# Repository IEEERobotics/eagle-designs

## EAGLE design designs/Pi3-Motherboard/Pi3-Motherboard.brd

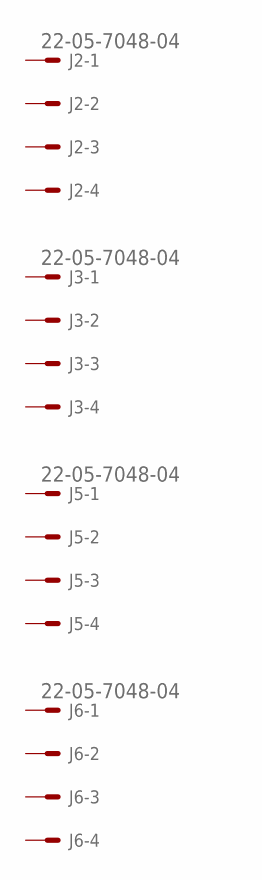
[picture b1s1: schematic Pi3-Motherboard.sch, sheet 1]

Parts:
J2, J3, J5, J6: 22-05-7048-04; 7395-04

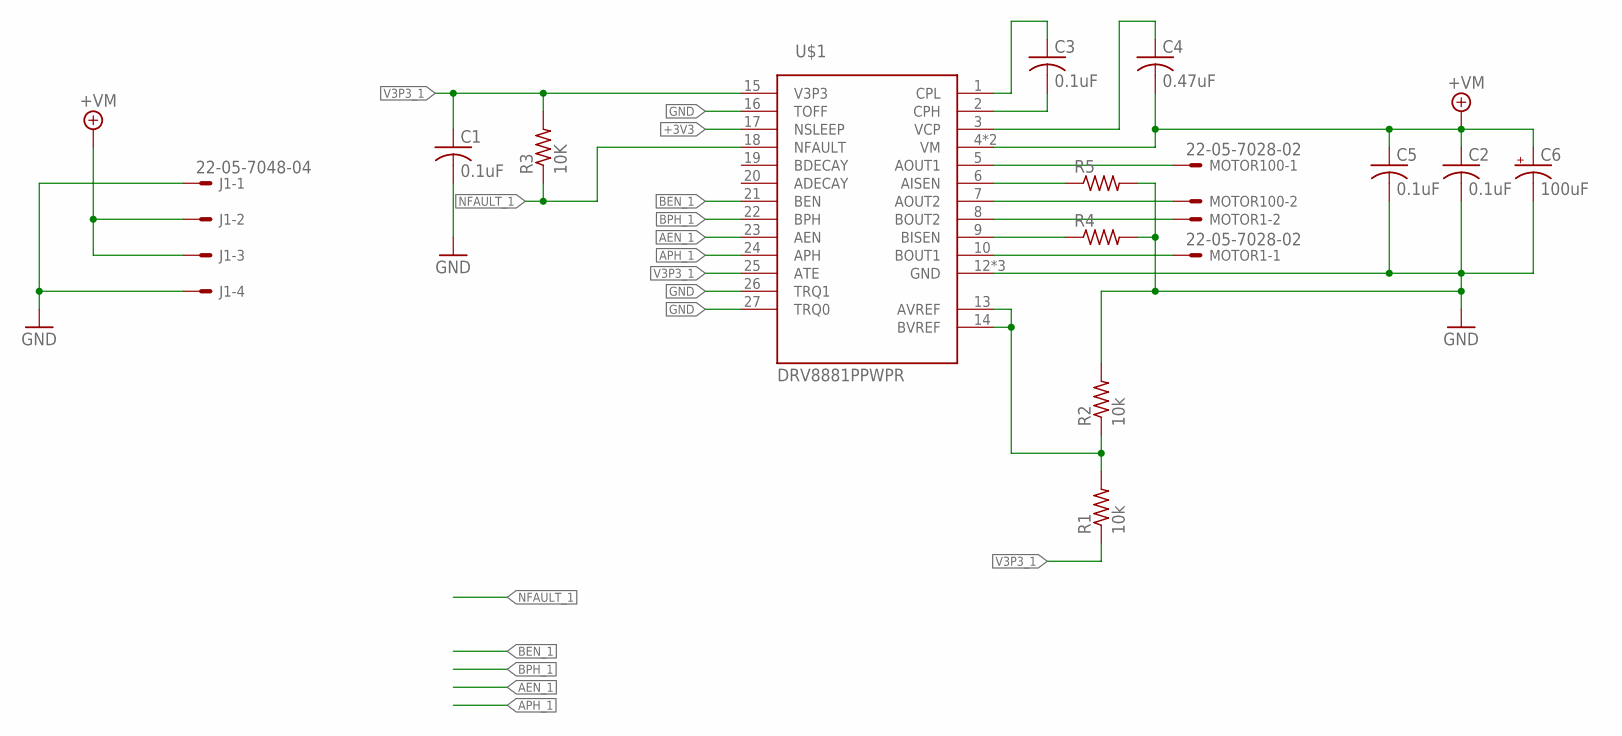
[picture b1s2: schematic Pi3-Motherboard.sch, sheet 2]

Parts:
C1, C2, C3, C5: 0.1uF; C0402
C4: 0.47uF; C0402
C6: 100uF; EIA7343
J1: 22-05-7048-04; 7395-04
MOTOR1, MOTOR100: 22-05-7028-02; 7395-02
R1, R2: 10k; R0402
R3: 10K; R1206
R4, R5: R-US_R1206; R1206
U$1: DRV8881PPWPR; TSSOP-28

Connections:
+3V3: U$1.17 (NSLEEP); also elsewhere on the board
+7V: C2.1, C4.2, C5.1, C6.A (+), J1.2, J1.3, U$1.4 (VM), U$1.11 (VM); also elsewhere on the board
AEN_1: U$1.23 (AEN)
APH_1: U$1.24 (APH)
BEN_1: U$1.21 (BEN)
BPH_1: U$1.22 (BPH)
GND: C1.2, C2.2, C5.2, C6.C (-), J1.1, J1.4, R2.2, R4.2, R5.2, U$1.12 (GND), U$1.16 (TOFF), U$1.26 (TRQ1), U$1.27 (TRQ0), U$1.28 (GND), U$1.EXP (GND); also elsewhere on the board
unnamed: R4.1, U$1.9 (BISEN)
unnamed 32: R5.1, U$1.6 (AISEN); also elsewhere on the board
unnamed: MOTOR100.1, U$1.5 (AOUT1)
unnamed: MOTOR100.2, U$1.7 (AOUT2)
unnamed: MOTOR1.2, U$1.8 (BOUT2)
unnamed: MOTOR1.1, U$1.10 (BOUT1)
unnamed: C3.2, U$1.2 (CPH)
unnamed: C3.1, U$1.1 (CPL)
unnamed: C4.1, U$1.3 (VCP)
unnamed: R1.2, R2.1, U$1.13 (AVREF), U$1.14 (BVREF)
NFAULT_1: R3.1, U$1.18 (NFAULT)
V3P3_1: C1.1, R1.1, R3.2, U$1.15 (V3P3), U$1.25 (ATE)

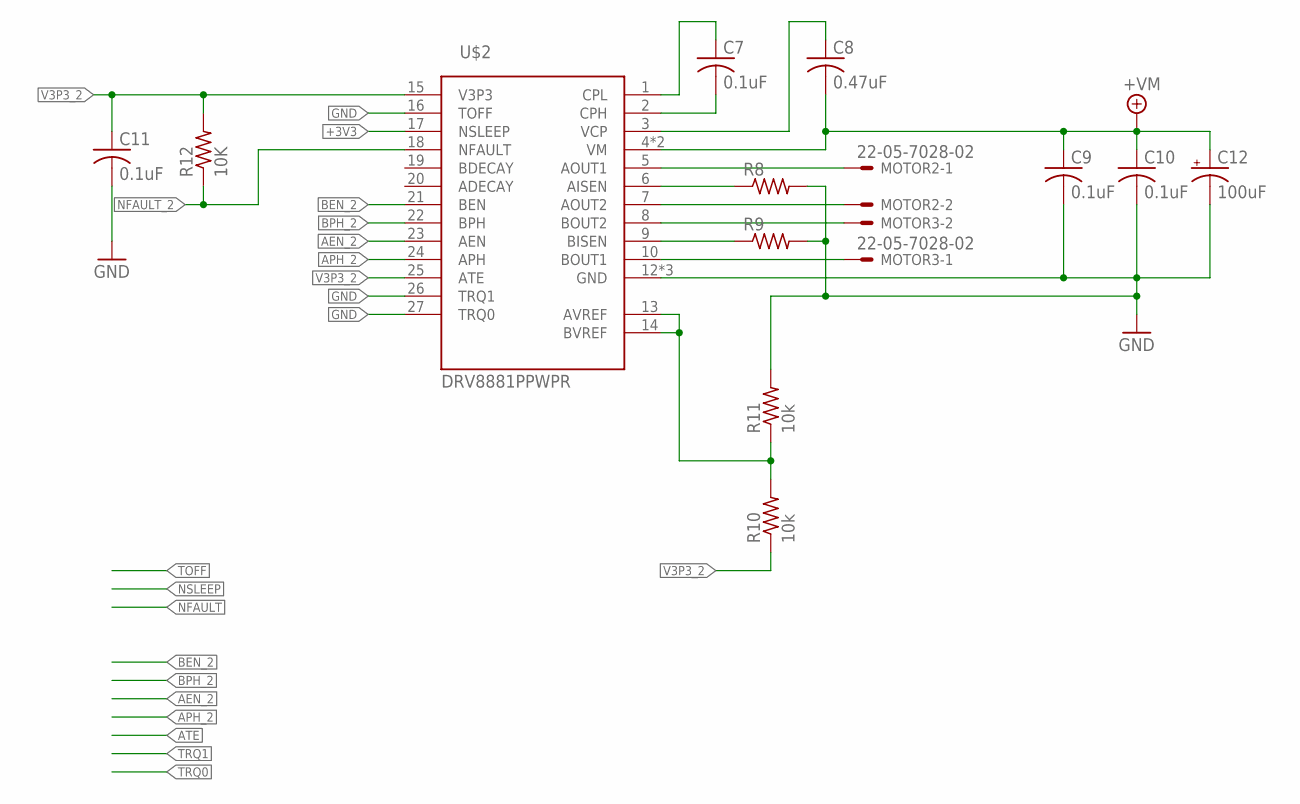
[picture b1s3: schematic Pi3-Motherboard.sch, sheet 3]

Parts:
C7, C9, C10, C11: 0.1uF; C0402
C8: 0.47uF; C0402
C12: 100uF; EIA7343
MOTOR2, MOTOR3: 22-05-7028-02; 7395-02
R8, R9: R-US_R1206; R1206
R10, R11: 10k; R0402
R12: 10K; R1206
U$2: DRV8881PPWPR; TSSOP-28

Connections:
+3V3: U$2.17 (NSLEEP); also elsewhere on the board
+7V: C8.2, C9.1, C10.1, C12.A (+), U$2.4 (VM), U$2.11 (VM); also elsewhere on the board
AEN_2: U$2.23 (AEN)
APH_2: U$2.24 (APH)
BEN_2: U$2.21 (BEN)
BPH_2: U$2.22 (BPH)
GND: C9.2, C10.2, C11.2, C12.C (-), R8.2, R9.2, R11.2, U$2.12 (GND), U$2.16 (TOFF), U$2.26 (TRQ1), U$2.27 (TRQ0), U$2.28 (GND), U$2.EXP (GND); also elsewhere on the board
unnamed: R9.1, U$2.9 (BISEN)
unnamed: R8.1, U$2.6 (AISEN)
unnamed: MOTOR2.1, U$2.5 (AOUT1)
unnamed: MOTOR2.2, U$2.7 (AOUT2)
unnamed: MOTOR3.2, U$2.8 (BOUT2)
unnamed: MOTOR3.1, U$2.10 (BOUT1)
unnamed: C7.2, U$2.2 (CPH)
unnamed: C7.1, U$2.1 (CPL)
unnamed: C8.1, U$2.3 (VCP)
unnamed: R10.2, R11.1, U$2.13 (AVREF), U$2.14 (BVREF)
NFAULT_2: R12.1, U$2.18 (NFAULT)
V3P3_2: C11.1, R10.1, R12.2, U$2.15 (V3P3), U$2.25 (ATE)

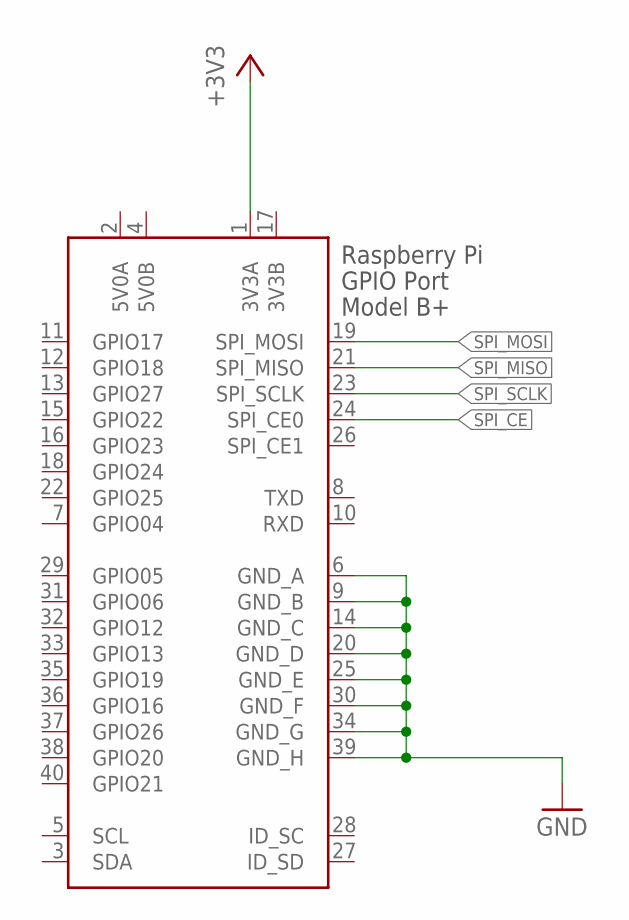
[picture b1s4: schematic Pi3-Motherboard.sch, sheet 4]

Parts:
X1: RASPI_BOARD_B+#_HD; RASPI_BOARD_B+HAT_DF

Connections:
3V3B: X1.17 (3V3B)
5V0A: X1.2 (5V0A)
5V0B: X1.4 (5V0B)
+3V3: X1.1 (3V3A); also elsewhere on the board
GND: X1.6 (GND_A), X1.9 (GND_B), X1.14 (GND_C), X1.20 (GND_D), X1.25 (GND_E), X1.30 (GND_F), X1.34 (GND_G), X1.39 (GND_H); also elsewhere on the board
SPI_CE: X1.24 (SPI_CE0)
SPI_MISO: X1.21 (SPI_MISO)
SPI_MOSI: X1.19 (SPI_MOSI)
SPI_SCLK: X1.23 (SPI_SCLK)

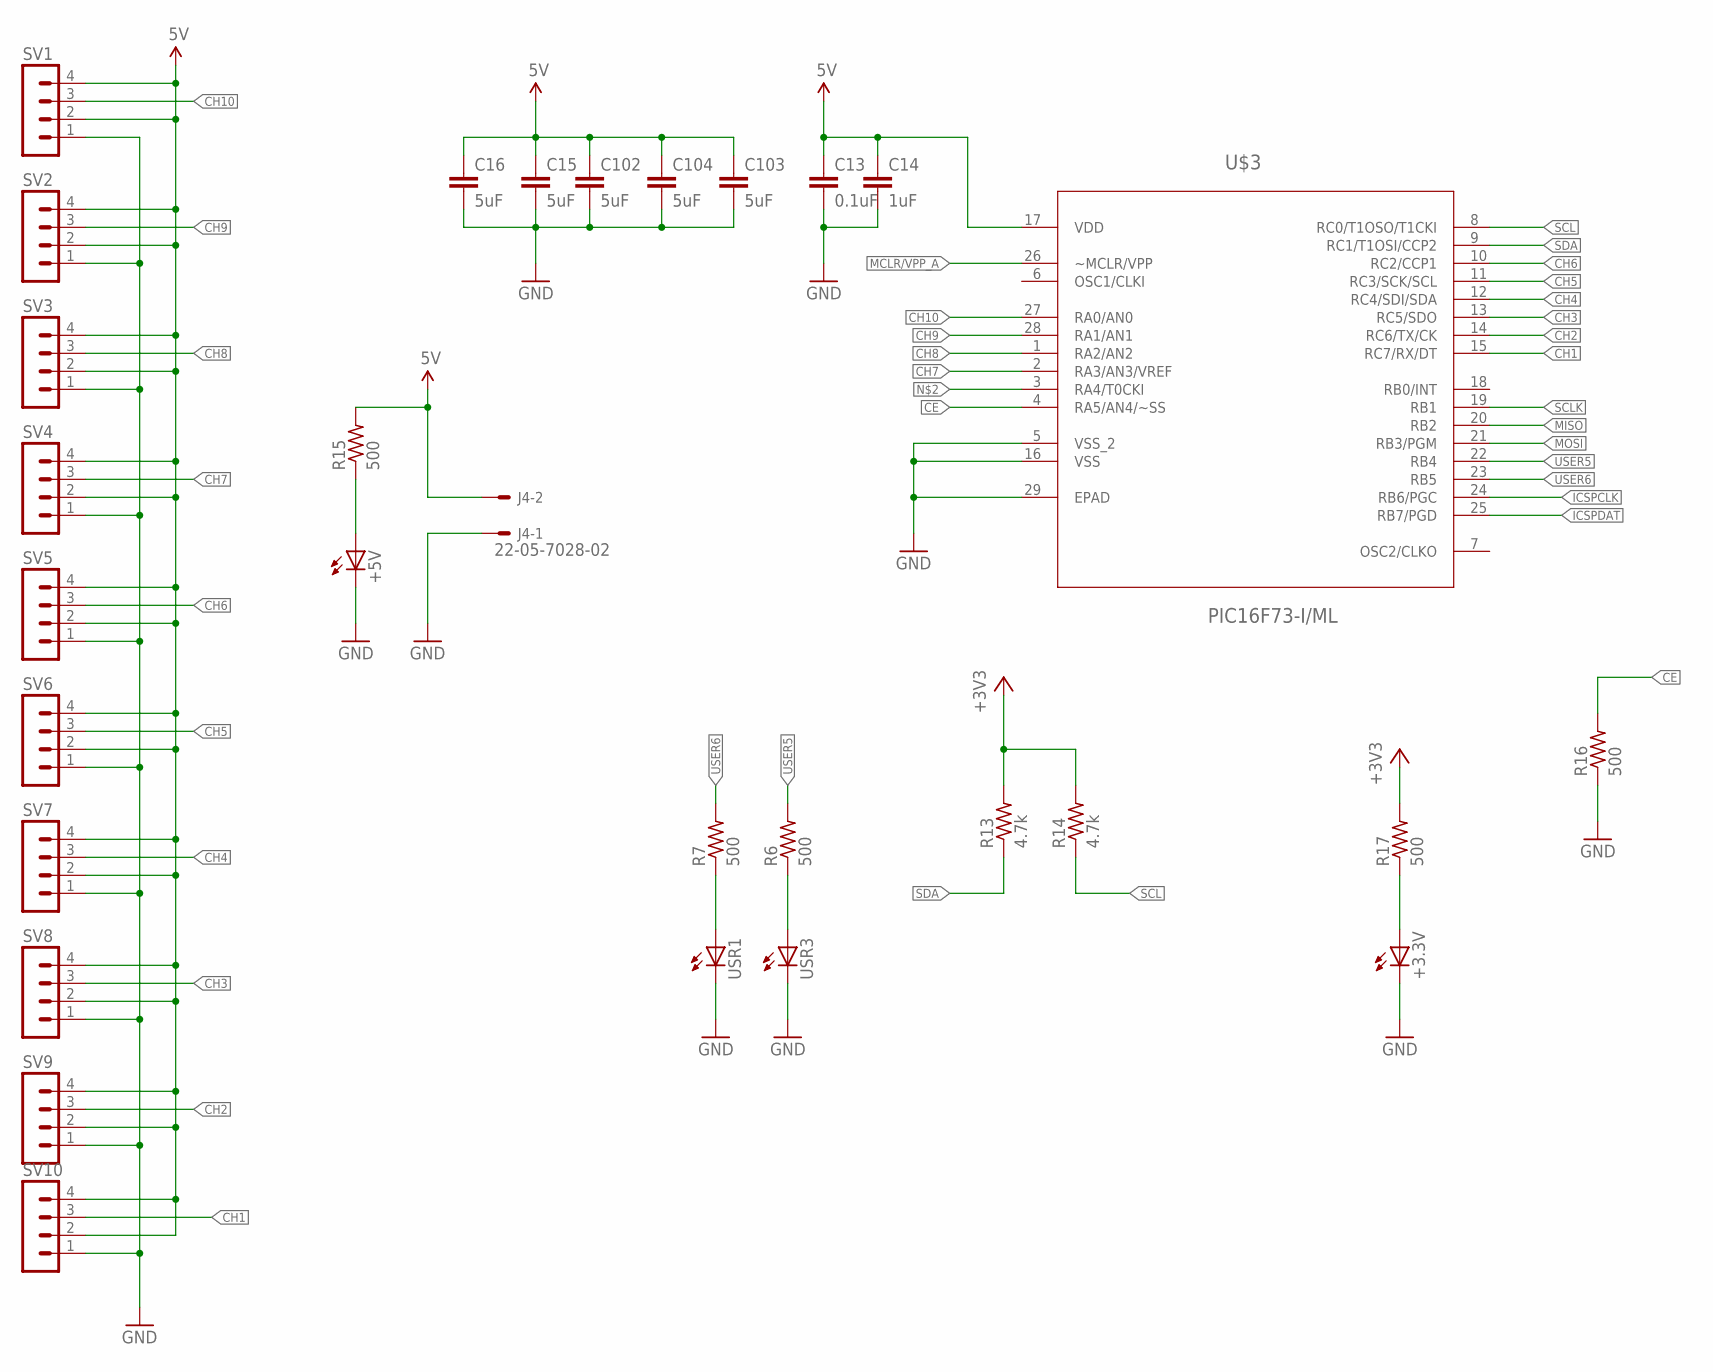
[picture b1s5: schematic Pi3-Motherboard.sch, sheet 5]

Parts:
+3.3V, +5V: LEDCHIP-LED0603; CHIP-LED0603
C13: 0.1uF; C0402
C14: 1uF; C0402
C15, C16, C102, C103, C104: 5uF; C0402
J4: 22-05-7028-02; 7395-02
R6, R7, R15, R16, R17: 500; R0402
R13, R14: 4.7k; R0402
SV1, SV2, SV3, SV4, SV5, SV6, SV7, SV8, SV9, SV10: MA04-1
U$3: PIC16F73-I/ML; QFN65P600X600X100-28N
USR1, USR3: LEDCHIP-LED0603; CHIP-LED0603

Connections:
5V: C13.1, C14.1, C15.1, C16.1, C102.1, C103.1, C104.1, J4.2, R15.2, SV1.2, SV1.4, SV2.2, SV2.4, SV3.2, SV3.4, SV4.2, SV4.4, SV5.2, SV5.4, SV6.2, SV6.4, SV7.2, SV7.4, SV8.2, SV8.4, SV9.2, SV9.4, SV10.2, SV10.4, U$3.17 (VDD)
+3V3: R13.2, R14.2, R17.2; also elsewhere on the board
CE: R16.2, U$3.4 (RA5/AN4/~SS)
CH1: SV10.3, U$3.15 (RC7/RX/DT)
CH2: SV9.3, U$3.14 (RC6/TX/CK)
CH3: SV8.3, U$3.13 (RC5/SDO)
CH4: SV7.3, U$3.12 (RC4/SDI/SDA)
CH5: SV6.3, U$3.11 (RC3/SCK/SCL)
CH6: SV5.3, U$3.10 (RC2/CCP1)
CH7: SV4.3, U$3.2 (RA3/AN3/VREF)
CH8: SV3.3, U$3.1 (RA2/AN2)
CH9: SV2.3, U$3.28 (RA1/AN1)
CH10: SV1.3, U$3.27 (RA0/AN0)
GND: +3.3V.C, +5V.C, C13.2, C14.2, C15.2, C16.2, C102.2, C103.2, C104.2, J4.1, R16.1, SV1.1, SV2.1, SV3.1, SV4.1, SV5.1, SV6.1, SV7.1, SV8.1, SV9.1, SV10.1, U$3.5 (VSS_2), U$3.16 (VSS), U$3.29 (EPAD), USR1.C, USR3.C; also elsewhere on the board
ICSPCLK: U$3.24 (RB6/PGC)
ICSPDAT: U$3.25 (RB7/PGD)
MCLR/VPP_A: U$3.26 (~MCLR/VPP)
MISO: U$3.20 (RB2)
MOSI: U$3.21 (RB3/PGM)
unnamed 32: U$3.3 (RA4/T0CKI); also elsewhere on the board
unnamed: R6.1, USR3.A
unnamed: R7.1, USR1.A
unnamed: +5V.A, R15.1
unnamed: +3.3V.A, R17.1
SCL: R14.1, U$3.8 (RC0/T1OSO/T1CKI)
SCLK: U$3.19 (RB1)
SDA: R13.1, U$3.9 (RC1/T1OSI/CCP2)
USER5: R6.2, U$3.22 (RB4)
USER6: R7.2, U$3.23 (RB5)

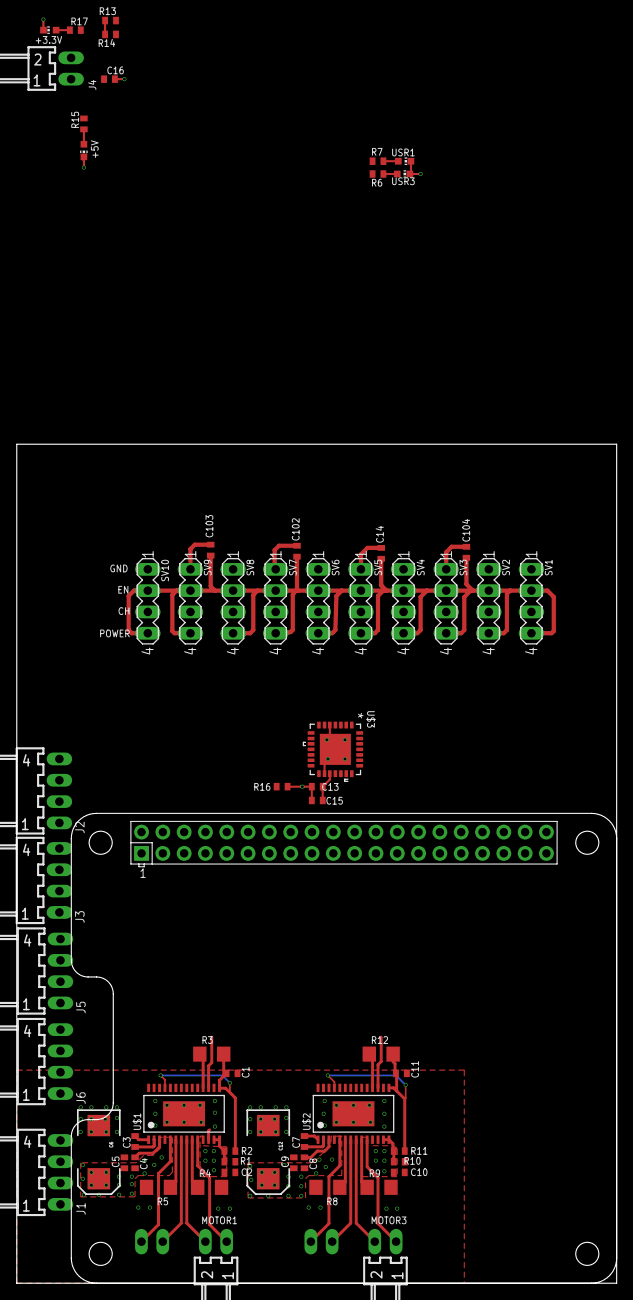
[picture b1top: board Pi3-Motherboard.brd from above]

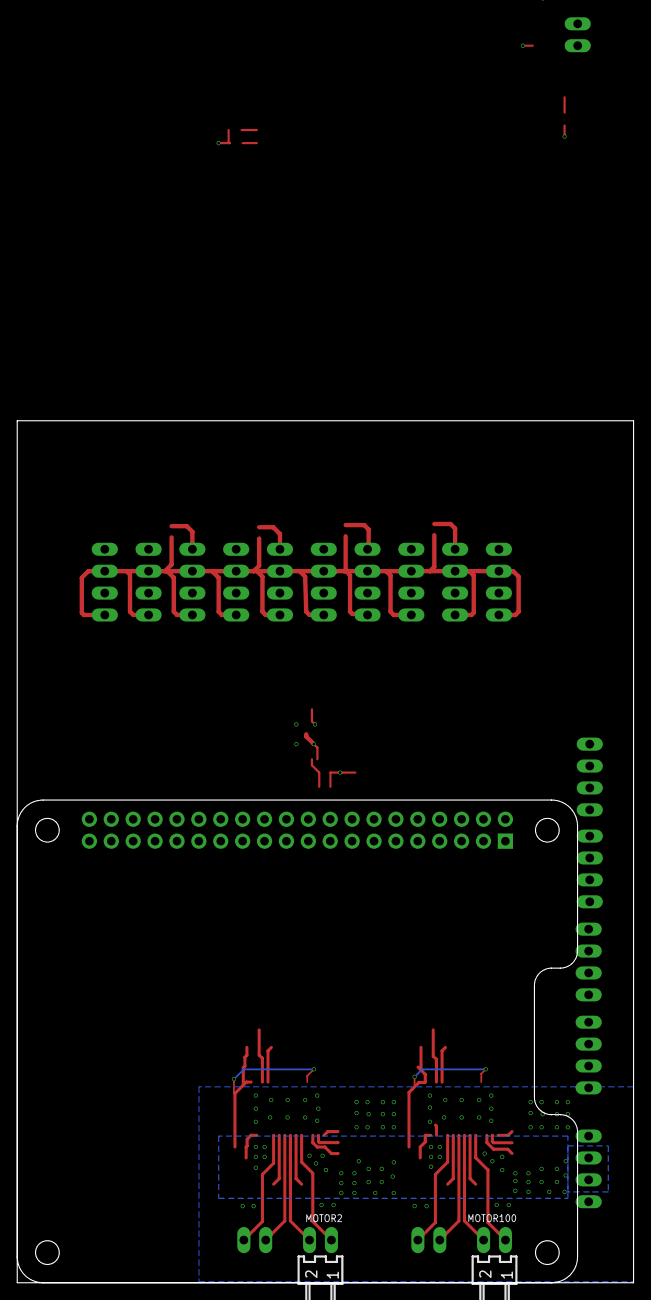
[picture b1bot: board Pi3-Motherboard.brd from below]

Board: 2 copper layers, 71.5 x 100.0 mm, 64 parts (2 on the bottom side), 47 nets.

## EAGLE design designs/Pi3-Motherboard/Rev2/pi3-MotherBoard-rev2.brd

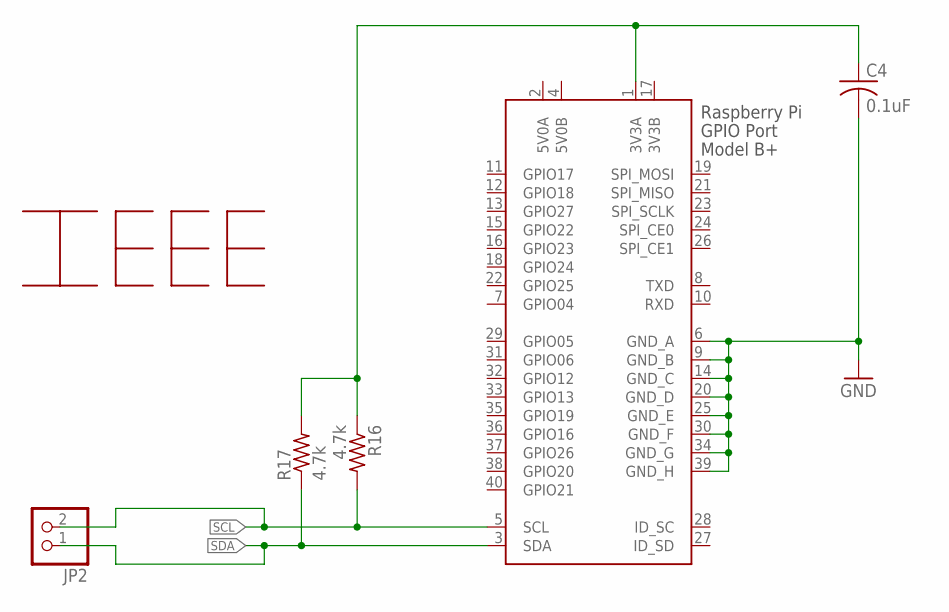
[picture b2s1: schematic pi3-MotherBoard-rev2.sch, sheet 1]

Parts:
C4: 0.1uF; C0805
JP2: PINHD-1X2; 1X02
R16, R17: 4.7k; R1206
U$1: LOGO; IEEE-LOGO
X1: RASPI_BOARD_B+#_FP; RASPI_BOARD_B+_FULL_PAD

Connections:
3V3B: X1.17 (3V3B)
5V0A: X1.2 (5V0A)
5V0B: X1.4 (5V0B)
+3V3: C4.1, R16.1, R17.2, X1.1 (3V3A); also elsewhere on the board
GND: C4.2, X1.6 (GND_A), X1.9 (GND_B), X1.14 (GND_C), X1.20 (GND_D), X1.25 (GND_E), X1.30 (GND_F), X1.34 (GND_G), X1.39 (GND_H); also elsewhere on the board
SCL: JP2.2, R16.2, X1.5 (SCL); also elsewhere on the board
SDA: JP2.1, R17.1, X1.3 (SDA); also elsewhere on the board

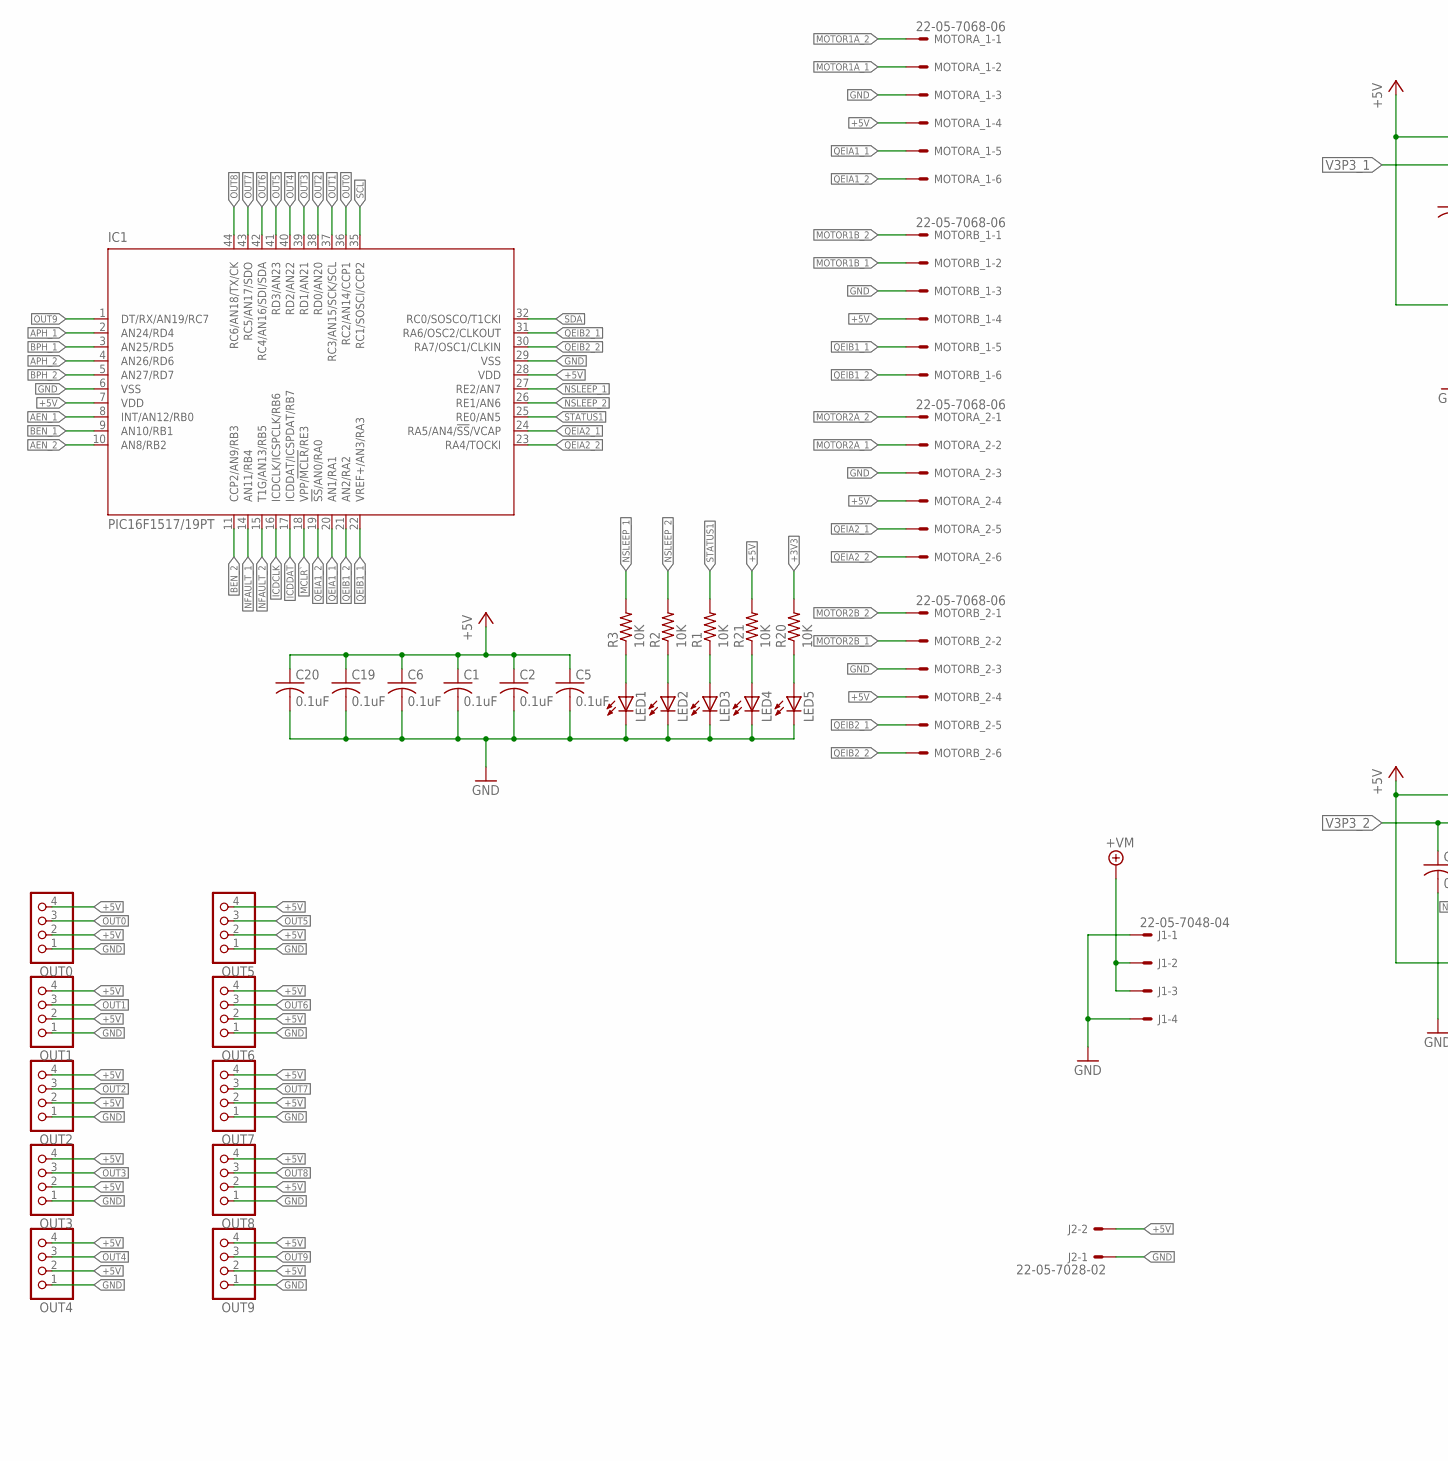
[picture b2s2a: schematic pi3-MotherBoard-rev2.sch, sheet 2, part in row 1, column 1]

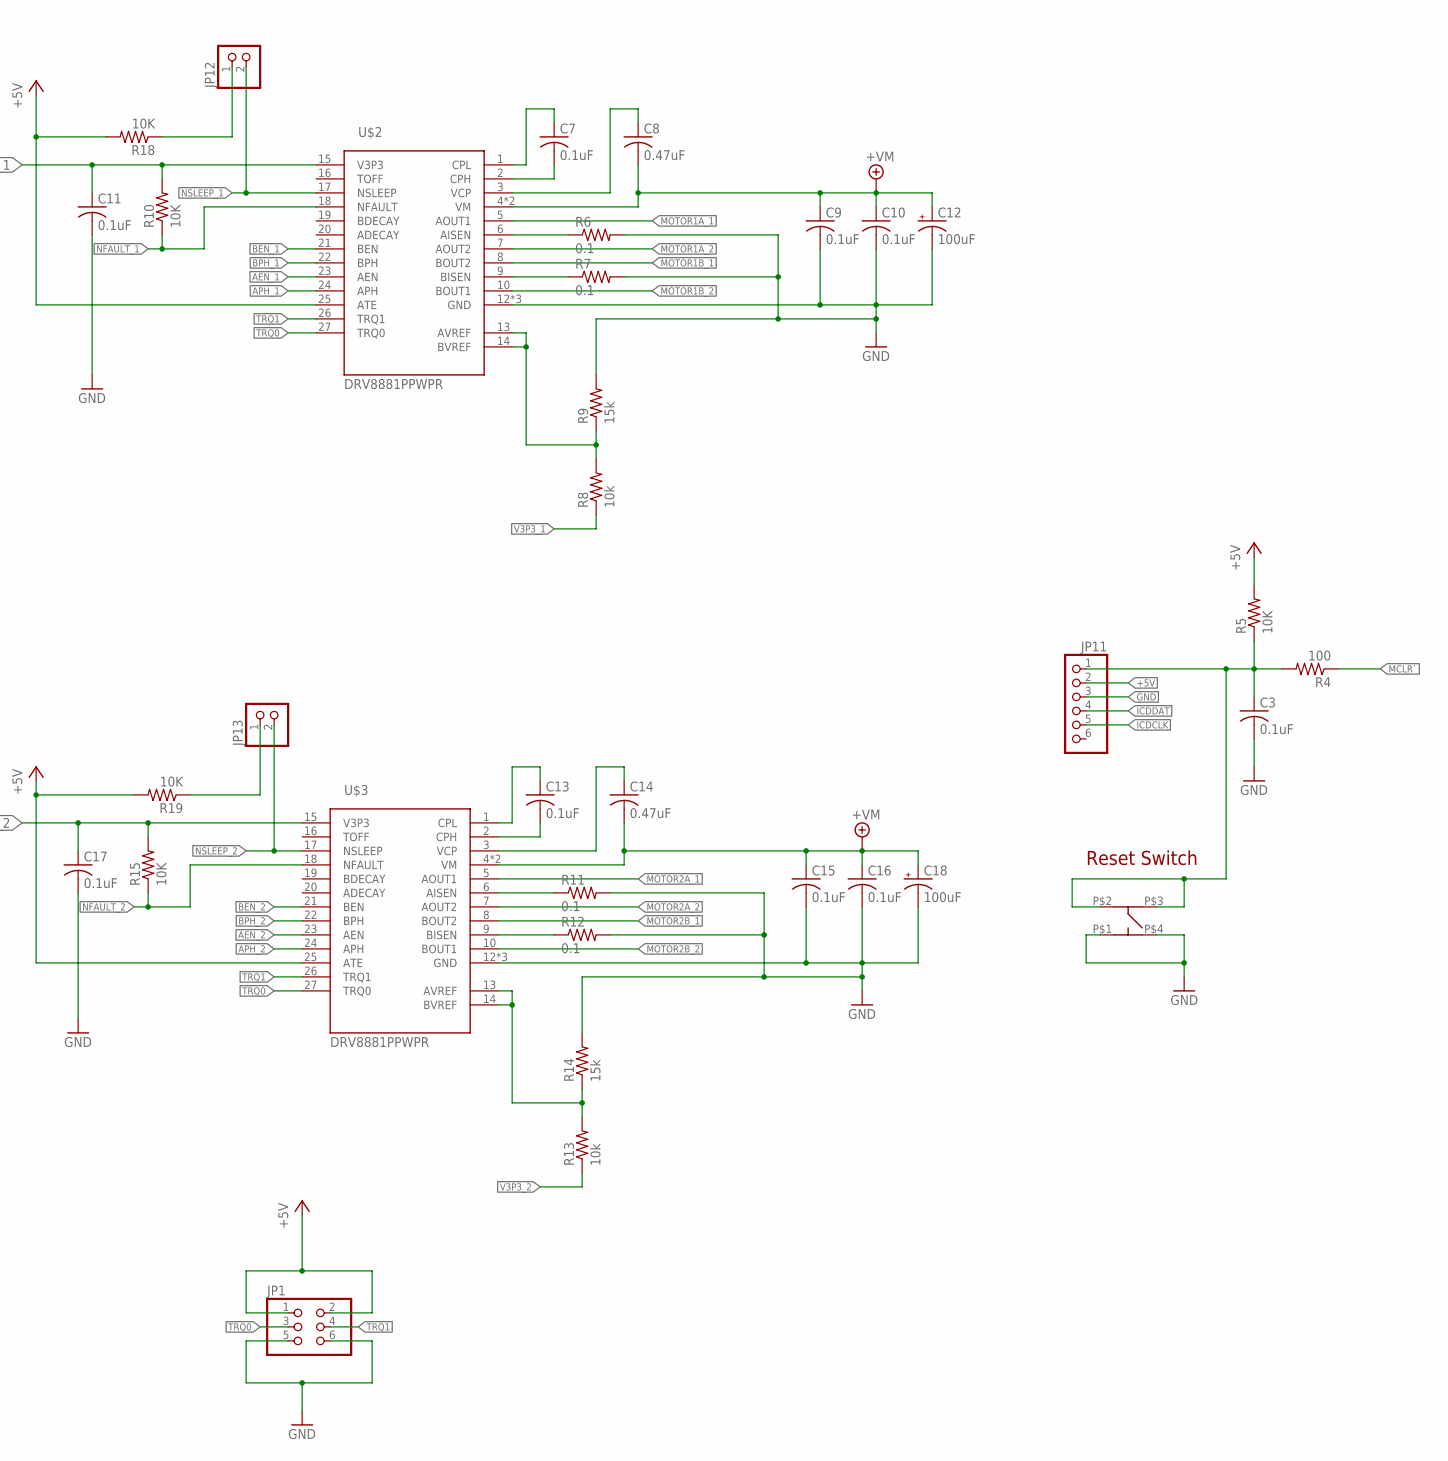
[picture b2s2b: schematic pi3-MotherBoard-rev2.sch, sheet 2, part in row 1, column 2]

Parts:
C1, C2, C3, C5, C6, C19, C20: 0.1uF; C0805
C7, C9, C10, C11, C13, C15, C16, C17: 0.1uF; C0402
C8, C14: 0.47uF; C0402
C12, C18: 100uF; EIA7343
IC1: PIC16F1517/19PT; TQFP44
J1: 22-05-7048-04; 7395-04
J2: 22-05-7028-02; 7395-02
JP1: PINHD-2X3; 2X03
JP11: PINHD-1X6/90; 1X06/90
JP12, JP13: PINHD-1X2; 1X02
LED1, LED2, LED3, LED4, LED5: LEDSML0603; SML0603
MOTORA_1, MOTORA_2: 22-05-7068-06; 7395-06
MOTORB_1, MOTORB_2: 22-05-7068-06; 7395-06
OUT0, OUT1, OUT2, OUT3, OUT4, OUT5, OUT6, OUT7, OUT8, OUT9: PINHD-1X4; 1X04
R1, R2, R3, R5, R10, R15, R18, R19, R20, R21: 10K; R1206
R4: 100; R1206
R6, R7, R11, R12: 0.1; R1206
R8, R13: 10k; R0402
R9, R14: 15k; R0402
TOUCH_RESET: RESET; MC32882_FINAL
U$2, U$3: DRV8881PPWPR; TSSOP-28

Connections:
+3V3: R20.2; also elsewhere on the board
+5V: C1.1, C2.1, C5.1, C6.1, C19.1, C20.1, IC1.7 (VDD), IC1.28 (VDD), J2.2, JP1.1, JP1.2, JP11.2, MOTORA_1.4, MOTORA_2.4, MOTORB_1.4, MOTORB_2.4, OUT0.2, OUT0.4, OUT1.2, OUT1.4, OUT2.2, OUT2.4, OUT3.2, OUT3.4, OUT4.2, OUT4.4, OUT5.2, OUT5.4, OUT6.2, OUT6.4, OUT7.2, OUT7.4, OUT8.2, OUT8.4, OUT9.2, OUT9.4, R5.2, R18.2, R19.2, R21.2, U$2.25 (ATE), U$3.25 (ATE)
+7V: C8.2, C9.1, C10.1, C12.A (+), C14.2, C15.1, C16.1, C18.A (+), J1.2, J1.3, U$2.4 (VM), U$2.11 (VM), U$3.4 (VM), U$3.11 (VM)
AEN_1: IC1.8 (INT/AN12/RB0), U$2.23 (AEN)
AEN_2: IC1.10 (AN8/RB2), U$3.23 (AEN)
APH_1: IC1.2 (AN24/RD4), U$2.24 (APH)
APH_2: IC1.4 (AN26/RD6), U$3.24 (APH)
BEN_1: IC1.9 (AN10/RB1), U$2.21 (BEN)
BEN_2: IC1.11 (CCP2/AN9/RB3), U$3.21 (BEN)
BPH_1: IC1.3 (AN25/RD5), U$2.22 (BPH)
BPH_2: IC1.5 (AN27/RD7), U$3.22 (BPH)
GND: C1.2, C2.2, C3.2, C5.2, C6.2, C9.2, C10.2, C11.2, C12.C (-), C15.2, C16.2, C17.2, C18.C (-), C19.2, C20.2, IC1.6 (VSS), IC1.29 (VSS), J1.1, J1.4, J2.1, JP1.5, JP1.6, JP11.3, LED1.C, LED2.C, LED3.C, LED4.C, LED5.C, MOTORA_1.3, MOTORA_2.3, MOTORB_1.3, MOTORB_2.3, OUT0.1, OUT1.1, OUT2.1, OUT3.1, OUT4.1, OUT5.1, OUT6.1, OUT7.1, OUT8.1, OUT9.1, R6.2, R7.2, R9.2, R11.2, R12.2, R14.2, TOUCH_RESET.P$1 (P1), TOUCH_RESET.P$4 (P4), U$2.12 (GND), U$2.28 (GND), U$2.EXP (GND), U$3.12 (GND), U$3.28 (GND), U$3.EXP (GND); also elsewhere on the board
ICDCLK: IC1.16 (ICDCLK/ICSPCLK/RB6), JP11.5
ICDDAT: IC1.17 (ICDDAT/ICSPDAT/RB7), JP11.4
MCLR: C3.1, JP11.1, R4.2, R5.1, TOUCH_RESET.P$2 (P2), TOUCH_RESET.P$3 (P3)
MCLR`: IC1.18 (VPP/!MCLR!/RE3), R4.1
MOTOR1A_1: MOTORA_1.2, U$2.5 (AOUT1)
MOTOR1A_2: MOTORA_1.1, U$2.7 (AOUT2)
MOTOR1B_1: MOTORB_1.2, U$2.8 (BOUT2)
MOTOR1B_2: MOTORB_1.1, U$2.10 (BOUT1)
MOTOR2A_1: MOTORA_2.2, U$3.5 (AOUT1)
MOTOR2A_2: MOTORA_2.1, U$3.7 (AOUT2)
MOTOR2B_1: MOTORB_2.2, U$3.8 (BOUT2)
MOTOR2B_2: MOTORB_2.1, U$3.10 (BOUT1)
unnamed: LED3.A, R1.1
unnamed: JP12.1, R18.1
unnamed: JP13.1, R19.1
unnamed: R7.1, U$2.9 (BISEN)
unnamed: LED5.A, R20.1
unnamed: LED2.A, R2.1
unnamed: LED1.A, R3.1
unnamed: LED4.A, R21.1
unnamed: R6.1, U$2.6 (AISEN)
unnamed: C7.2, U$2.2 (CPH)
unnamed: C7.1, U$2.1 (CPL)
unnamed: C8.1, U$2.3 (VCP)
unnamed: R8.2, R9.1, U$2.13 (AVREF), U$2.14 (BVREF)
unnamed: R12.1, U$3.9 (BISEN)
unnamed: R11.1, U$3.6 (AISEN)
unnamed: C13.2, U$3.2 (CPH)
unnamed: C13.1, U$3.1 (CPL)
unnamed: C14.1, U$3.3 (VCP)
unnamed: R13.2, R14.1, U$3.13 (AVREF), U$3.14 (BVREF)
NFAULT_1: IC1.14 (AN11/RB4), R10.1, U$2.18 (NFAULT)
NFAULT_2: IC1.15 (T1G/AN13/RB5), R15.1, U$3.18 (NFAULT)
NSLEEP_1: IC1.27 (RE2/AN7), JP12.2, R3.2, U$2.17 (NSLEEP)
NSLEEP_2: IC1.26 (RE1/AN6), JP13.2, R2.2, U$3.17 (NSLEEP)
OUT0: IC1.36 (RC2/AN14/CCP1), OUT0.3
OUT1: IC1.37 (RC3/AN15/SCK/SCL), OUT1.3
OUT2: IC1.38 (RD0/AN20), OUT2.3
OUT3: IC1.39 (RD1/AN21), OUT3.3
OUT4: IC1.40 (RD2/AN22), OUT4.3
OUT5: IC1.41 (RD3/AN23), OUT5.3
OUT6: IC1.42 (RC4/AN16/SDI/SDA), OUT6.3
OUT7: IC1.43 (RC5/AN17/SDO), OUT7.3
OUT8: IC1.44 (RC6/AN18/TX/CK), OUT8.3
OUT9: IC1.1 (DT/RX/AN19/RC7), OUT9.3
QEIA1_1: IC1.20 (AN1/RA1), MOTORA_1.5
QEIA1_2: IC1.19 (!SS!/AN0/RA0), MOTORA_1.6
QEIA2_1: IC1.24 (RA5/AN4/!SS!/VCAP), MOTORA_2.5
QEIA2_2: IC1.23 (RA4/TOCKI), MOTORA_2.6
QEIB1_1: IC1.22 (VREF+/AN3/RA3), MOTORB_1.5
QEIB1_2: IC1.21 (AN2/RA2), MOTORB_1.6
QEIB2_1: IC1.31 (RA6/OSC2/CLKOUT), MOTORB_2.5
QEIB2_2: IC1.30 (RA7/OSC1/CLKIN), MOTORB_2.6
SCL: IC1.35 (RC1/SOSCI/CCP2); also elsewhere on the board
SDA: IC1.32 (RC0/SOSCO/T1CKI); also elsewhere on the board
STATUS1: IC1.25 (RE0/AN5), R1.2
TRQ0: JP1.3, U$2.27 (TRQ0), U$3.27 (TRQ0)
TRQ1: JP1.4, U$2.26 (TRQ1), U$3.26 (TRQ1)
V3P3_1: C11.1, R8.1, R10.2, U$2.15 (V3P3)
V3P3_2: C17.1, R13.1, R15.2, U$3.15 (V3P3)

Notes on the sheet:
Reset Switch

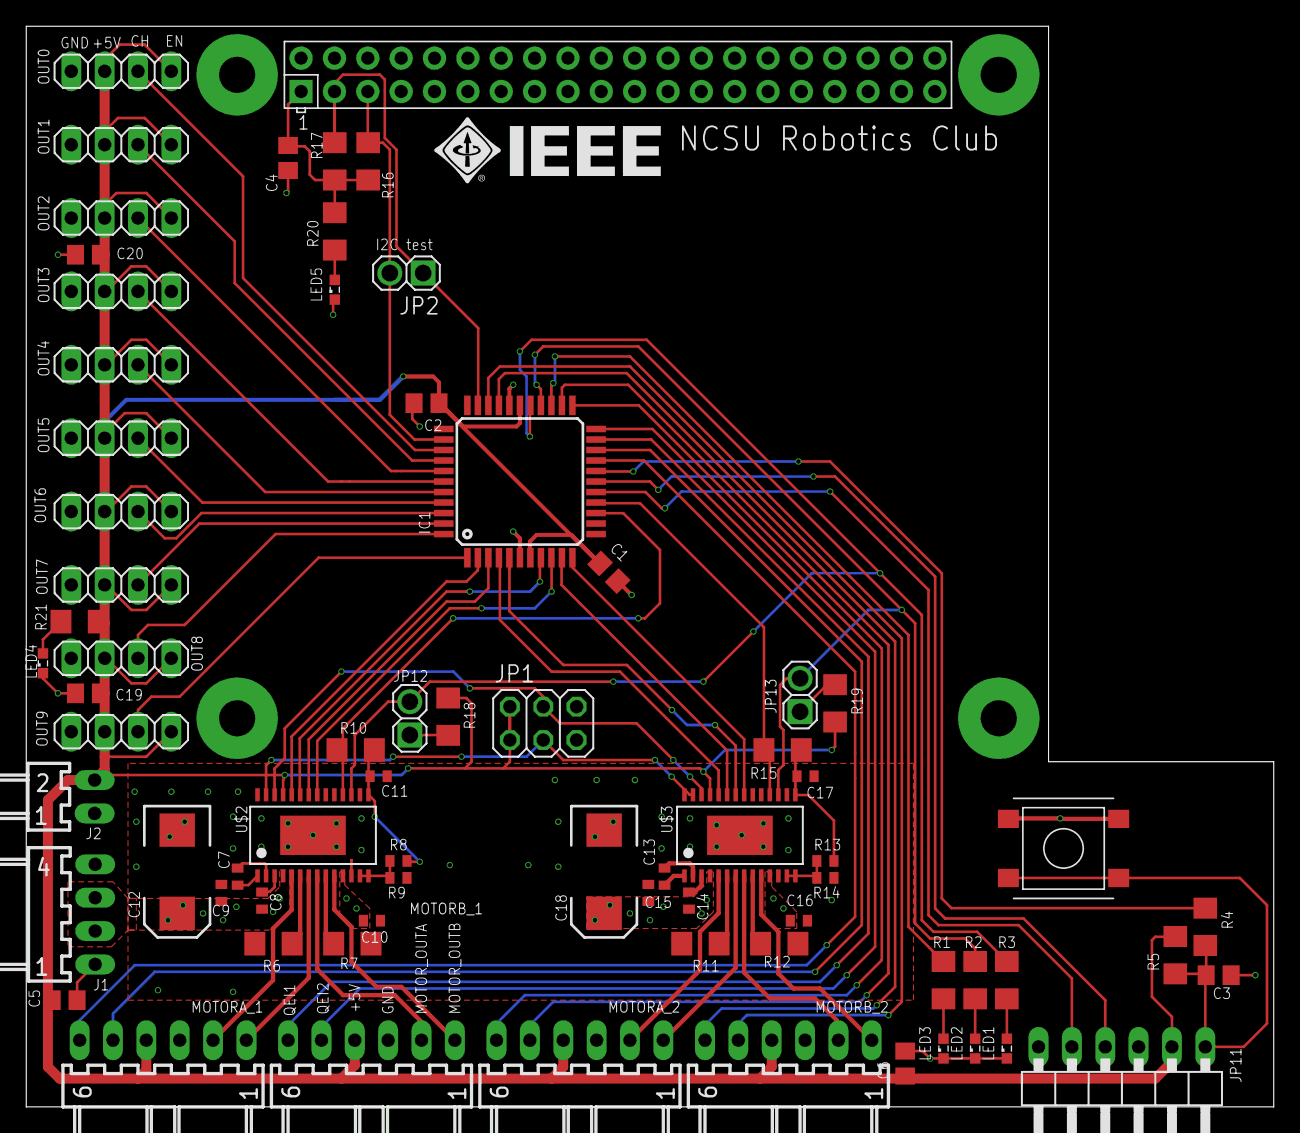
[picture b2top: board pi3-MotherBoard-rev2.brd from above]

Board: 2 copper layers, 95.0 x 82.3 mm, 73 parts (0 on the bottom side), 72 nets.

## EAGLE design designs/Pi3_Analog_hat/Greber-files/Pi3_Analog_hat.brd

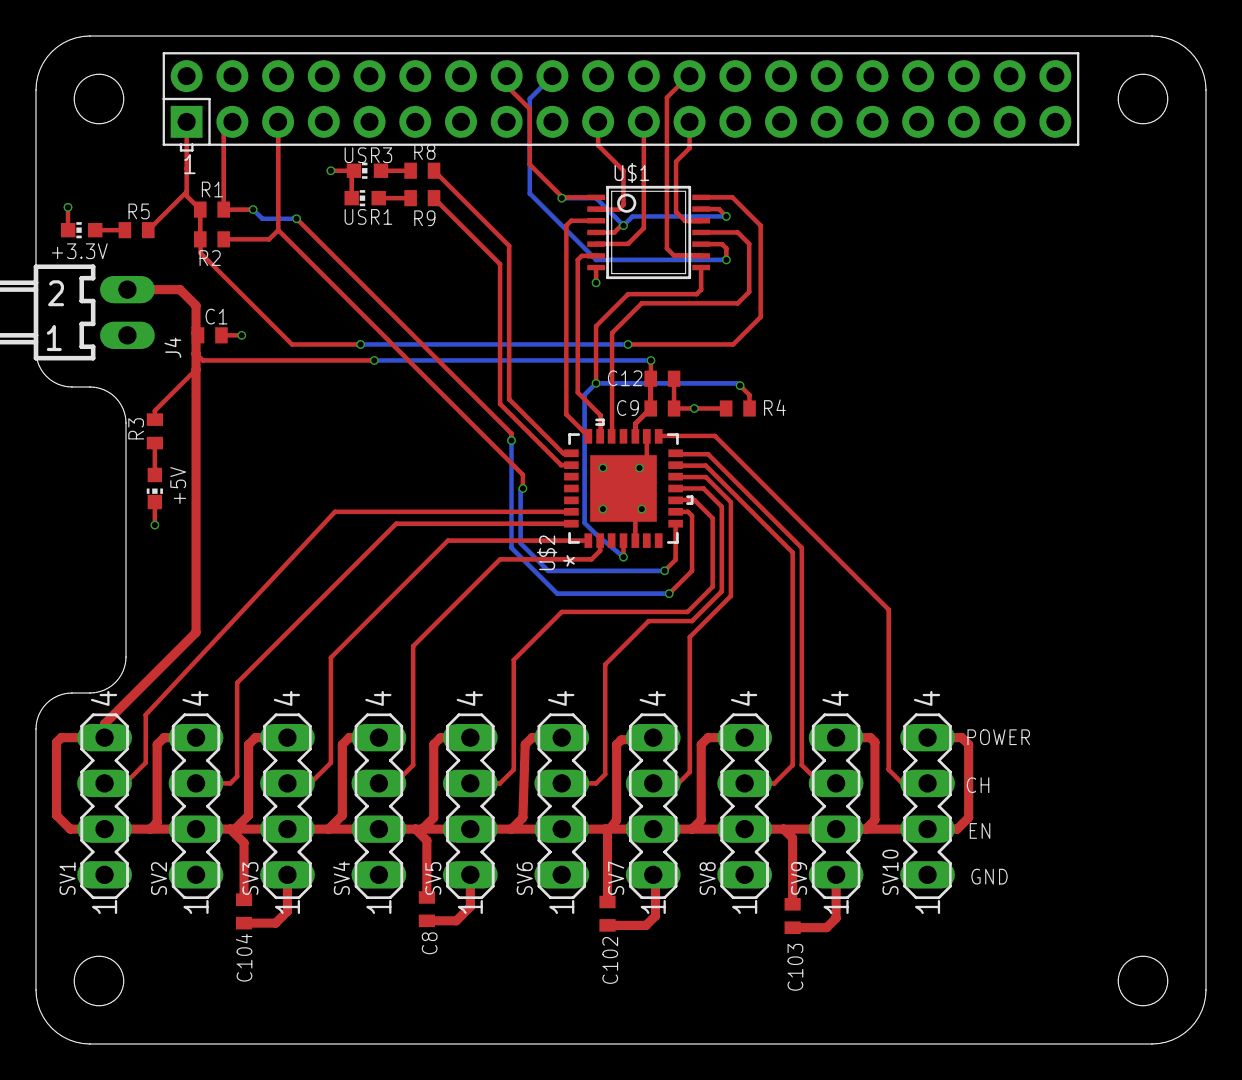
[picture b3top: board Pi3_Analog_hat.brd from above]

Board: 2 copper layers, 65.0 x 56.0 mm, 32 parts (0 on the bottom side), 31 nets.

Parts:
+3.3V, +5V: CHIP-LED0603
C1, C12, C102, C103, C104: 5uF; C0402
C8: 1uF; C0402
C9: 0.1uF; C0402
J4: 22-05-7028-02; 7395-02
R1, R2: 4.7k; R0402
R3, R4, R5, R8, R9: 500; R0402
SV1, SV2, SV3, SV4, SV5, SV6, SV7, SV8, SV9, SV10: MA04-1
U$1: SN74CB3T3125PW; TSSOP-14
U$2: PIC16F73-I/ML; QFN65P600X600X100-28N
USR1, USR3: CHIP-LED0603
X1: RASPI_BOARD_B+#_HD; RASPI_BOARD_B+HAT_DF

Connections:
5V: C1.1, C8.1, C9.1, C12.1, C102.1, C103.1, C104.1, J4.2, R3.2, SV1.2, SV1.4, SV2.2, SV2.4, SV3.2, SV3.4, SV4.2, SV4.4, SV5.2, SV5.4, SV6.2, SV6.4, SV7.2, SV7.4, SV8.2, SV8.4, SV9.2, SV9.4, SV10.2, SV10.4, U$2.17
+3V3: R1.2, R2.2, R5.2, U$1.14, X1.1
CE: R4.2, U$1.8, U$2.4
CE_EN: U$1.10, X1.18
CH1: SV10.3, U$2.15
CH2: SV9.3, U$2.14
CH3: SV8.3, U$2.13
CH4: SV7.3, U$2.12
CH5: SV6.3, U$2.11
CH6: SV5.3, U$2.10
CH7: SV4.3, U$2.2
CH8: SV3.3, U$2.1
CH9: SV2.3, U$2.28
CH10: SV1.3, U$2.27
GND: +3.3V.C, +5V.C, C1.2, C8.2, C9.2, C12.2, C102.2, C103.2, C104.2, J4.1, R4.1, SV1.1, SV2.1, SV3.1, SV4.1, SV5.1, SV6.1, SV7.1, SV8.1, SV9.1, SV10.1, U$1.7, U$2.5, U$2.16, U$2.29, USR1.C, USR3.C, X1.6, X1.9, X1.14, X1.20, X1.25, X1.30, X1.34, X1.39
MISO: U$1.6, U$2.20
MOSI: U$1.3, U$2.21
unnamed: +5V.A, R3.1
unnamed: +3.3V.A, R5.1
unnamed: R8.1, USR3.A
unnamed: R9.1, USR1.A
SCL: R2.1, U$2.8, X1.5
SCLK: U$1.11, U$2.19
SDA: R1.1, U$2.9, X1.3
SPI_CE: U$1.9, X1.24
SPI_EN: U$1.1, U$1.4, U$1.13, X1.16
SPI_MISO: U$1.5, X1.21
SPI_MOSI: U$1.2, X1.19
SPI_SCLK: U$1.12, X1.23
USER5: R8.2, U$2.22
USER6: R9.2, U$2.23

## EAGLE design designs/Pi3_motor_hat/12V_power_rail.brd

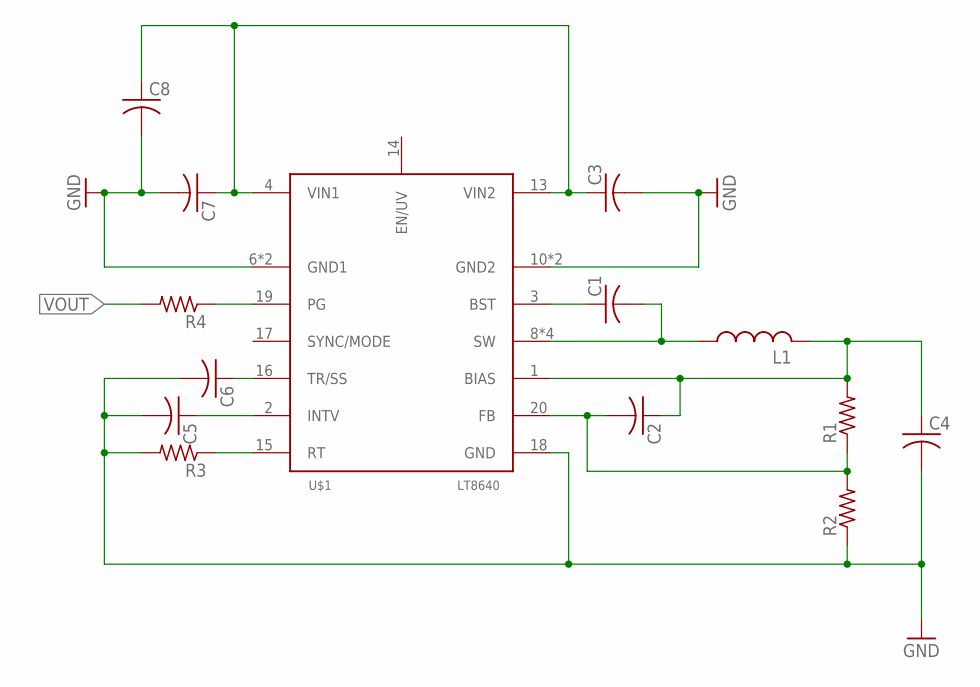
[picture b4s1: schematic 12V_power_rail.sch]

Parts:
C1, C2, C3, C5, C6, C7: C-USC0402; C0402
C4: C-USC1210; C1210
C8: C-USC0603; C0603
L1: L-USIHLP2525EZER4R7M01; IHLP2525EZER4R7M01-FOOT
R1, R2, R3, R4: R-US_R0402; R0402
U$1: LT8640; LT8640_FOOT

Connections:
GND: C3.2, C4.2, C5.2, C6.2, C7.2, C8.2, R2.1, R3.2, U$1.6 (GND1), U$1.7 (GND1), U$1.10 (GND2), U$1.11 (GND2), U$1.18 (GND)
unnamed: C1.1, U$1.3 (BST)
unnamed: C1.2, L1.1, U$1.8 (SW), U$1.9 (SW), U$1.21 (SW), U$1.22 (SW)
unnamed: R4.1, U$1.19 (PG)
unnamed: C2.2, R1.1, R2.2, U$1.20 (FB)
unnamed: C6.1, U$1.16 (TR/SS)
unnamed: C5.1, U$1.2 (INTV)
unnamed: R3.1, U$1.15 (RT)
VIN: C3.1, C7.1, C8.1, U$1.4 (VIN1), U$1.13 (VIN2)
VOUT: C2.1, C4.1, L1.2, R1.2, R4.2, U$1.1 (BIAS)

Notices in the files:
parts and their libraries:
SparkFun-Capacitors: Licensing: Creative Commons ShareAlike 4.0 International - https://creativecommons.org/licenses/by-sa/4.0
